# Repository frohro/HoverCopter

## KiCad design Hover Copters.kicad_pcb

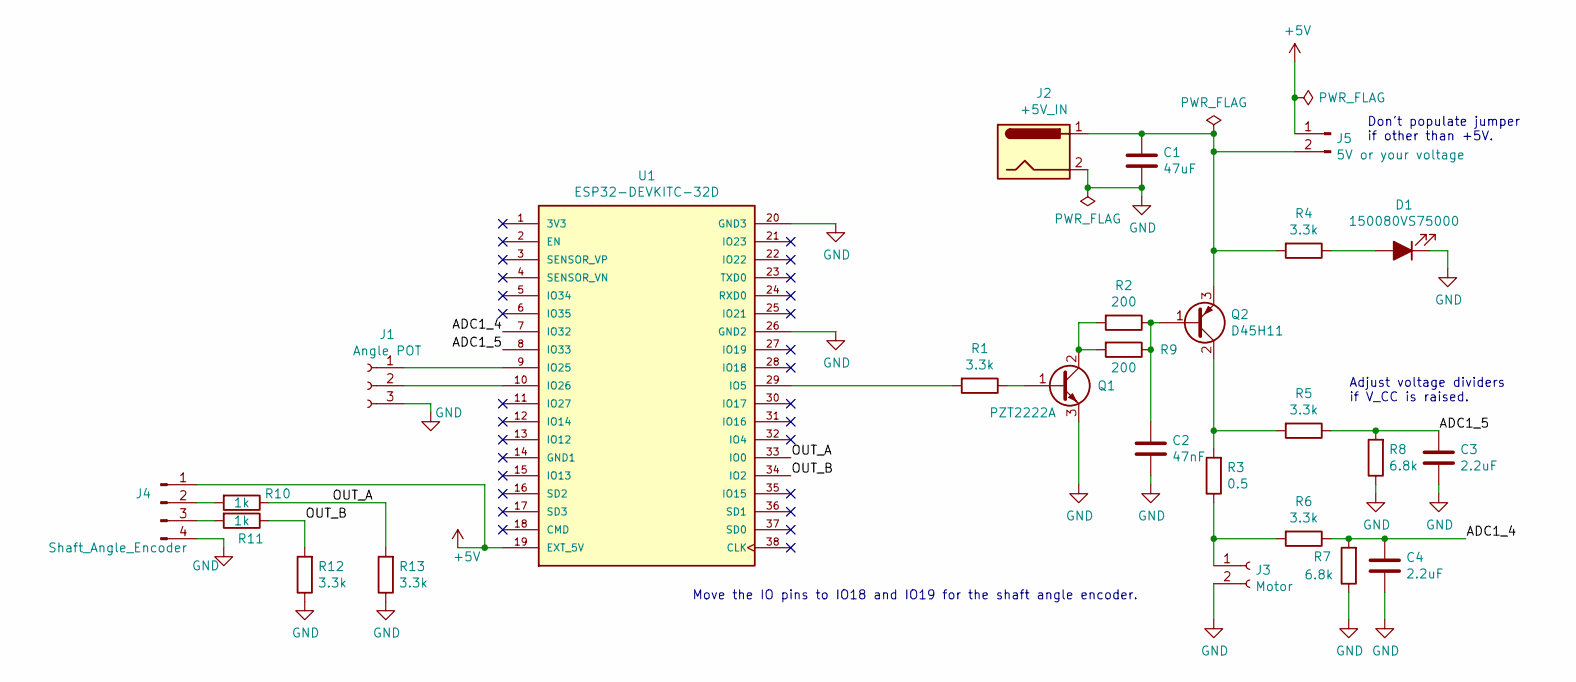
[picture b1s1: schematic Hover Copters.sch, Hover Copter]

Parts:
C1: 47uF; C_0805_2012Metric
C2: 47nF; C_0805_2012Metric
C3, C4: 2.2uF; C_0805_2012Metric
D1: 150080VS75000; LED_0805_2012Metric
J1: Angle POT; PinHeader_1x03_P2.54mm_Vertical
J2: +5V_IN; BarrelJack_Horizontal
J3: Motor; PinSocket_1x02_P2.54mm_Vertical
J4: Shaft_Angle_Encoder; PinHeader_1x04_P2.54mm_Vertical
J5: 5V or your voltage; PinHeader_1x02_P2.54mm_Vertical
Q1: PZT2222A; SOT-223-3_TabPin2
Q2: D45H11; TO-220-3_Vertical
R1, R4, R5, R6, R12, R13: 3.3k; R_0805_2012Metric
R2, R9: 200; R_0805_2012Metric
R3: 0.5; R_0805_2012Metric
R7, R8: 6.8k; R_0805_2012Metric
R10, R11: 1k; R_0805_2012Metric
U1: ESP32-DEVKITC-32D; MODULE_ESP32-DEVKITC-32D; PARTREV 4

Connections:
+5V: J4.1, J5.1, U1.19 (EXT_5V)
/ADC1_4: C4.1, R6.1, R7.2, U1.7 (IO32)
/ADC1_5: C3.1, R5.1, R8.2, U1.8 (IO33)
/OUT_A: R10.1, R13.2, U1.33 (IO0)
/OUT_B: R11.1, R12.2, U1.34 (IO2)
GND: C1.2, C2.2, C3.2, C4.2, D1.1 (K), J1.3, J2.2, J3.2, J4.4, Q1.3 (E), R7.1, R8.1, R12.1, R13.1, U1.20 (GND3), U1.26 (GND2)
unnamed: C1.1, J2.1, J5.2, Q2.3 (E), R4.2
unnamed: C2.1, Q2.1 (B), R2.1, R9.1
unnamed: D1.2 (A), R4.1
unnamed: J1.1, U1.9 (IO25)
unnamed: J1.2, U1.10 (IO26)
unnamed: J3.1, R3.1, R6.2
unnamed: J4.2, R10.2
unnamed: J4.3, R11.2
unnamed: Q1.1 (B), R1.1
unnamed: Q1.2 (C), R2.2, R9.2
unnamed: Q2.2 (C), R3.2, R5.2
unnamed: R1.2, U1.29 (IO5)

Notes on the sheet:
Adjust voltage dividers if V_CC is raised.
Don't populate jumper if other than +5V.
Move the IO pins to IO18 and IO19 for the shaft angle encoder.

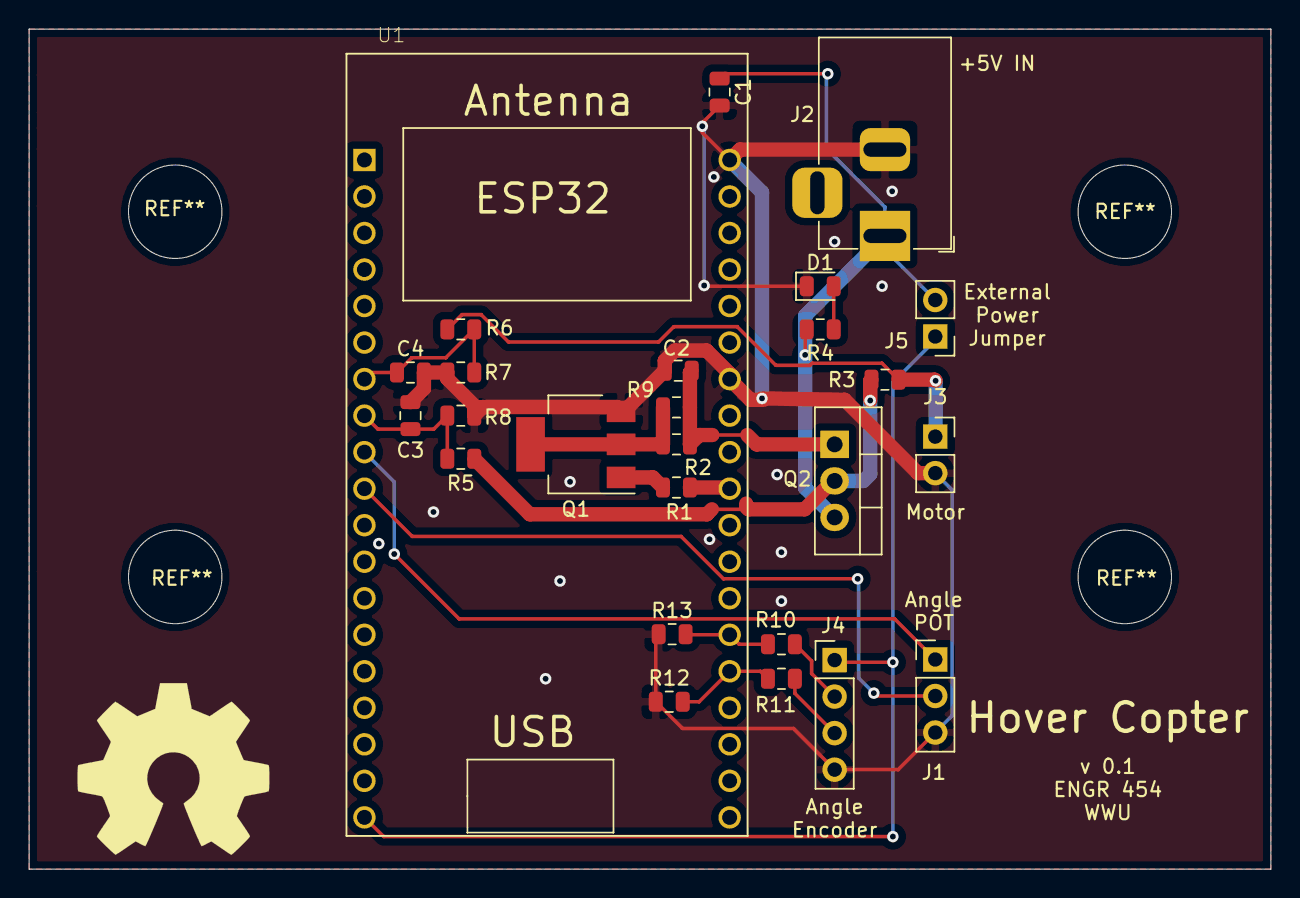
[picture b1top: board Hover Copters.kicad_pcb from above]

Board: 2 copper layers, 86.4 x 58.4 mm, 26 parts (0 on the bottom side), 18 nets.

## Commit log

2021-04-29 Note about fixing the IO0 being pulled up.
2021-04-29 Added encoder datasheet.
